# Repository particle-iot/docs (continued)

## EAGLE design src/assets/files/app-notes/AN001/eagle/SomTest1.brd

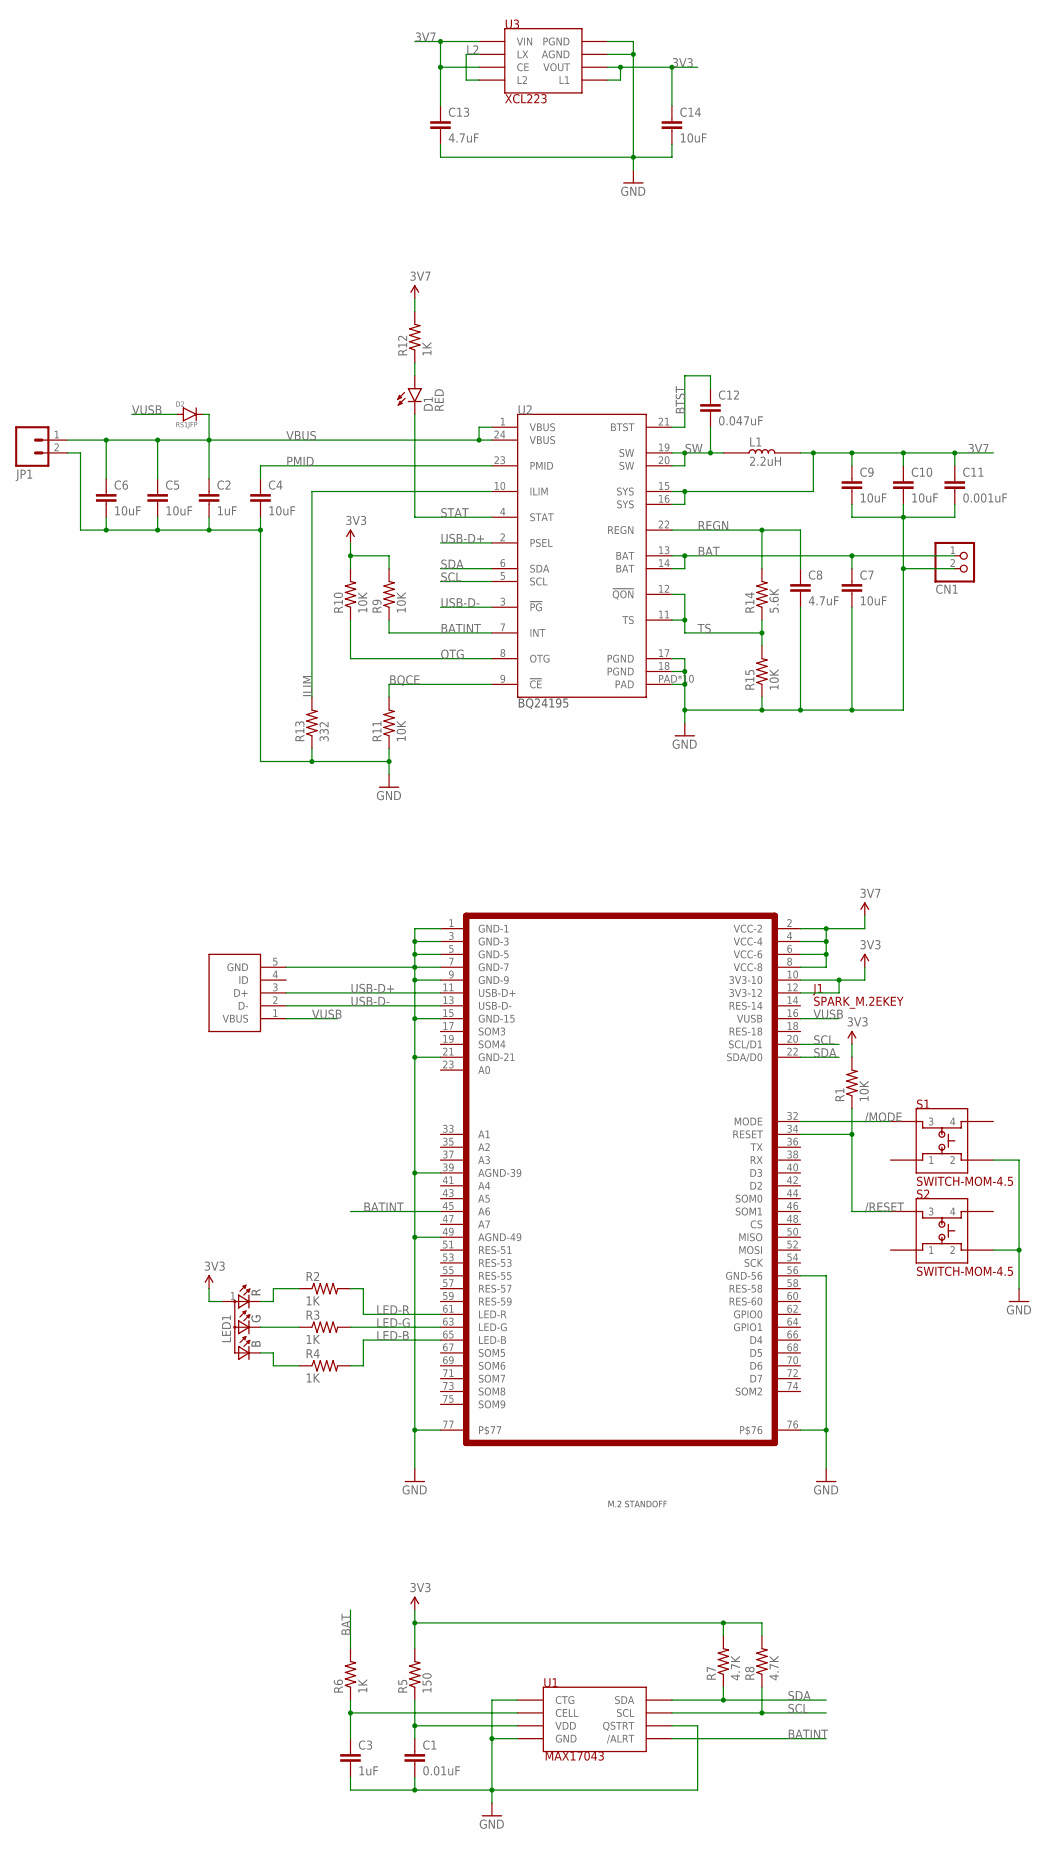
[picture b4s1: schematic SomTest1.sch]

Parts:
C1: 0.01uF; 0603-CAP
C2, C3: 1uF; 0603-CAP
C4, C5, C6, C7, C9, C10, C14: 10uF; 0603-CAP
C8, C13: 4.7uF; 0603-CAP
C11: 0.001uF; 0603-CAP
C12: 0.047uF; 0603-CAP
CN1: JST_2PIN-THM; JST-PH-2-THM
D1: RED; LED-0603
D2: RS1JFP; SOD-123HE-ON
J1: SPARK_M.2EKEY; SPARK_M.2EKEY-LESS-CREAM
JP1: M02PTH; 1X02
L1: 2.2uH; 1008-BOURNS
LED1: LED-RGB-CREE-SMD
R1, R9, R10, R11, R15: 10K; 0603-RES
R2, R3, R4, R6, R12: 1K; 0603-RES
R5: 150; 0603-RES
R7, R8: 4.7K; 0603-RES
R13: 332; 0603-RES
R14: 5.6K; 0603-RES
S1, S2: SWITCH-MOM-4.5
U1: MAX17043; 9UCSP-MAXIM
U2: BQ24195; 24VFQN-TI
U3: XCL223; REG-XCL223-LESS-CREAM
U$1: M2-STANDOFF
U$3: USB-MICRO-B-SOCKET-AMPHENOL; USB-B-SMT-AMPHENOL

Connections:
3V3: C14.1, J1.10 (3V3-10), J1.12 (3V3-12), LED1.1 (A), R1.2, R5.2, R7.2, R8.2, R9.2, R10.2, U3.3 (VOUT), U3.7 (L1)
3V7: C9.1, C10.1, C11.1, C13.1, J1.2 (VCC-2), J1.4 (VCC-4), J1.6 (VCC-6), J1.8 (VCC-8), L1.2, R12.2, U2.15 (SYS), U2.16 (SYS), U3.4 (CE), U3.6 (VIN)
/MODE: J1.32 (MODE), S1.3
/RESET: J1.34 (RESET), R1.1, S2.3
BAT: C7.1, CN1.1 (2), R6.2, U2.13 (BAT), U2.14 (BAT)
BATINT: J1.45 (A6), R9.1, U1.C1 (/ALRT), U2.7 (INT)
BQCE: R11.2, U2.9 (!CE)
BTST: C12.1, U2.21 (BTST)
GND: C1.2, C2.2, C3.2, C4.2, C5.2, C6.2, C7.2, C8.2, C9.2, C10.2, C11.2, C13.2, C14.2, CN1.2 (1), J1.1 (GND-1), J1.3 (GND-3), J1.5 (GND-5), J1.7 (GND-7), J1.9 (GND-9), J1.15 (GND-15), J1.21 (GND-21), J1.39 (AGND-39), J1.49 (AGND-49), J1.56 (GND-56), J1.76, J1.77, JP1.2, R11.1, R13.1, R15.1, S1.2, S2.2, U1.A3 (CTG), U1.B1 (QSTRT), U1.C3 (GND), U2.17 (PGND), U2.18 (PGND), U2.PAD, U2.PAD@1 (PAD), U2.PAD@2 (PAD), U2.PAD@3 (PAD), U2.PAD@4 (PAD), U2.PAD@5 (PAD), U2.PAD@6 (PAD), U2.PAD@7 (PAD), U2.PAD@8 (PAD), U2.PAD@9 (PAD), U3.1 (PGND), U3.2 (AGND), U$3.5 (GND)
ILIM: R13.2, U2.10 (ILIM)
L2: U3.5 (LX), U3.8 (L2)
LED-B: J1.65 (LED-B), R4.2
LED-G: J1.63 (LED-G), R3.2
LED-R: J1.61 (LED-R), R2.2
unnamed: LED1.3 (G), R3.1
unnamed: C3.1, R6.1, U1.B3 (CELL)
unnamed: C1.1, R5.1, U1.C2 (VDD)
unnamed: LED1.4 (R), R2.1
unnamed: D1.A, R12.1
unnamed: LED1.2 (B), R4.1
OTG: R10.1, U2.8 (OTG)
PMID: C4.1, U2.23 (PMID)
REGN: C8.1, R14.2, U2.22 (REGN)
SCL: J1.20 (SCL/D1), R8.1, U1.A2 (SCL), U2.5 (SCL)
SDA: J1.22 (SDA/D0), R7.1, U1.A1 (SDA), U2.6 (SDA)
STAT: D1.C, U2.4 (STAT)
SW: C12.2, L1.1, U2.19 (SW), U2.20 (SW)
TS: R14.1, R15.2, U2.11 (TS), U2.12 (!QON)
USB-D+: J1.11 (USB-D+), U2.2 (PSEL), U$3.3 (D+)
USB-D-: J1.13 (USB-D-), U2.3 (!PG), U$3.2 (D-)
VBUS: C2.1, C5.1, C6.1, D2.1 (CATHODE), JP1.1, U2.1 (VBUS), U2.24 (VBUS)
VUSB: D2.2 (ANODE), J1.16 (VUSB), U$3.1 (VBUS)

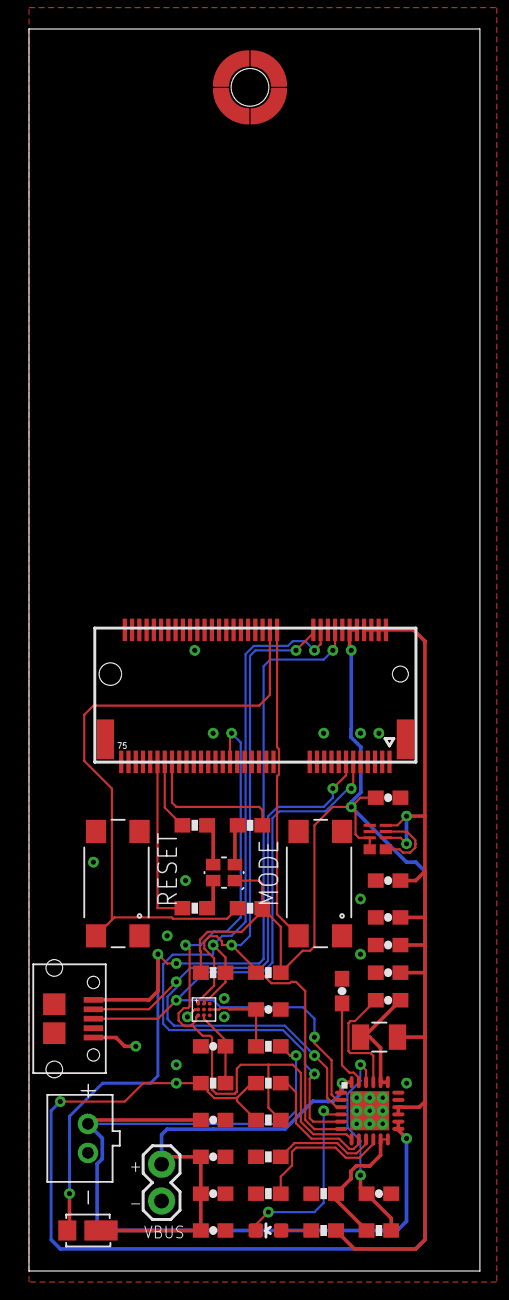
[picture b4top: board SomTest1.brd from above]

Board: 2 copper layers, 31.1 x 85.6 mm, 43 parts (0 on the bottom side), 32 nets.

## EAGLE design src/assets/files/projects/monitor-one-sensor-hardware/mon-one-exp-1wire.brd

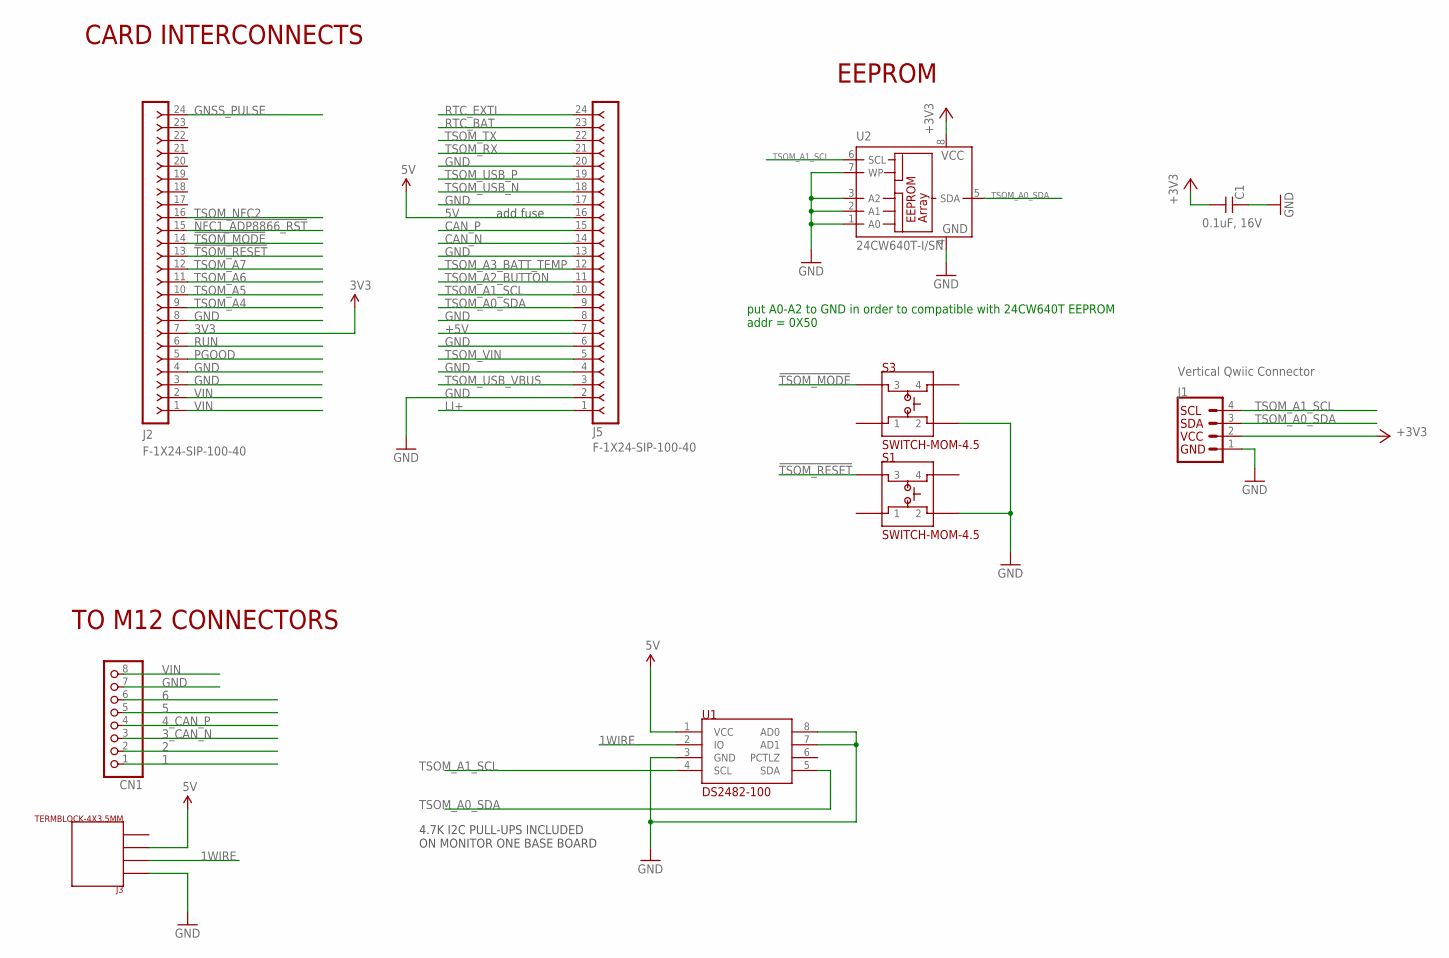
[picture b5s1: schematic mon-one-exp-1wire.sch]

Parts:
C1: 0.1uF, 16V; C0603_P
CN1: JST_8PIN; JSTPH8
J1: Vertical Qwiic Connector; JST04_1MM_VERT
J2, J5: F-1X24-SIP-100-40; SIP-100-24-40
J3: TERMBLOCK-4X3.5MM
S1, S3: SWITCH-MOM-4.5
U1: DS2482-100; 8-SOIC-MAXIM
U2: 24CW640T-I/SN; SO-08

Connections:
1: CN1.1
1WIRE: J3.2, U1.2 (IO)
2: CN1.2
3V3: C1.1, J1.2, J2.7, U2.8 (VCC)
3_CAN_N: CN1.3
4_CAN_P: CN1.4
5: CN1.5
5V: J3.3, J5.16, U1.1 (VCC)
6: CN1.6
!NFC1_ADP8866_RST: J2.15
!TSOM_MODE: J2.14, S3.3
!TSOM_RESET: J2.13, S1.3
+5V: J5.7
CAN_N: J5.14
CAN_P: J5.15
GND: C1.2, CN1.7, J1.1, J2.3, J2.4, J2.8, J3.1, J5.2, J5.4, J5.6, J5.8, J5.13, J5.17, J5.20, S1.2, S3.2, U1.3 (GND), U1.7 (AD1), U1.8 (AD0), U2.1 (A0), U2.2 (A1), U2.3 (A2), U2.4 (GND), U2.7 (WP)
GNSS_PULSE: J2.24
LI+: J5.1
PGOOD: J2.5
RTC_BAT: J5.23
RTC_EXTI: J5.24
RUN: J2.6
TSOM_A0_SDA: J1.3, J5.9, U1.5 (SDA), U2.5 (SDA)
TSOM_A1_SCL: J1.4, J5.10, U1.4 (SCL), U2.6 (SCL)
TSOM_A2_BUTTON: J5.11
TSOM_A3_BATT_TEMP: J5.12
TSOM_A4: J2.9
TSOM_A5: J2.10
TSOM_A6: J2.11
TSOM_A7: J2.12
TSOM_NFC2: J2.16
TSOM_RX: J5.21
TSOM_TX: J5.22
TSOM_USB_N: J5.18
TSOM_USB_P: J5.19
TSOM_USB_VBUS: J5.3
TSOM_VIN: J5.5
VIN: CN1.8, J2.1, J2.2

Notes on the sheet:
add fuse
CARD INTERCONNECTS
EEPROM
put A0-A2 to GND in order to compatible with 24CW640T EEPROM addr = 0X50
TO M12 CONNECTORS
4.7K I2C PULL-UPS INCLUDED ON MONITOR ONE BASE BOARD

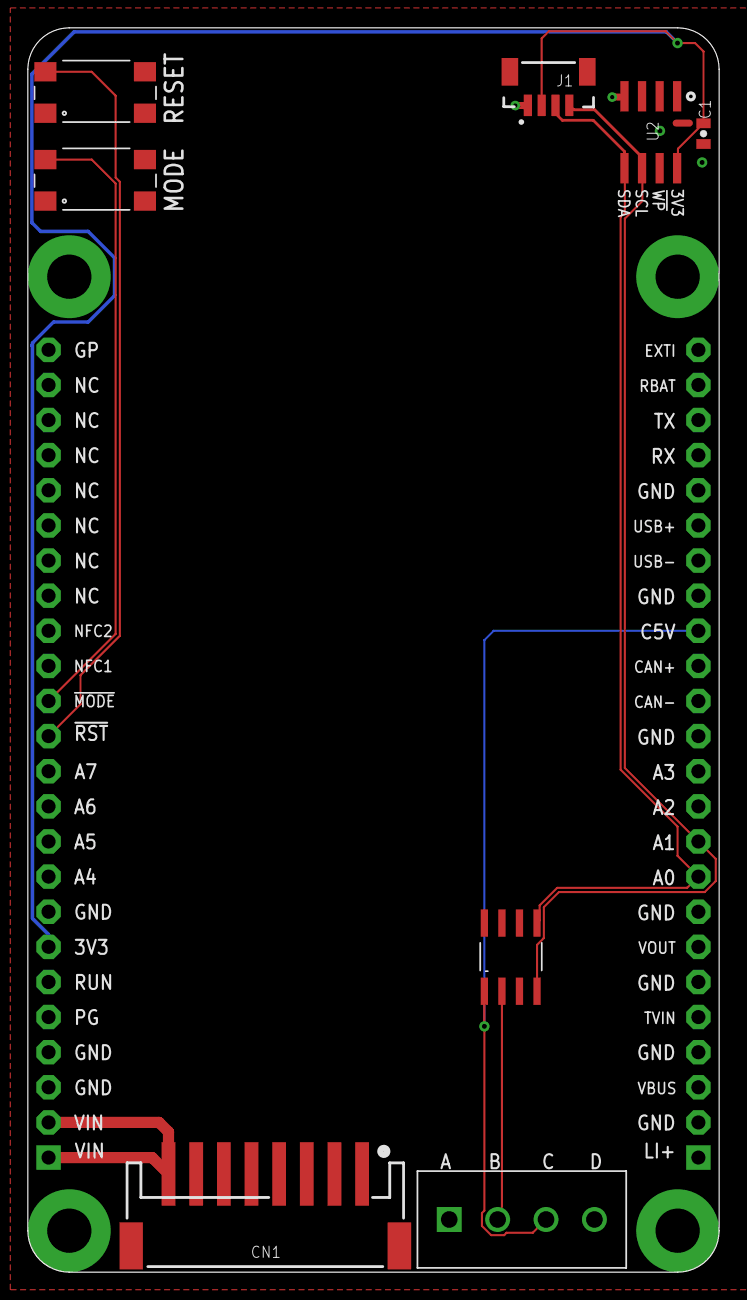
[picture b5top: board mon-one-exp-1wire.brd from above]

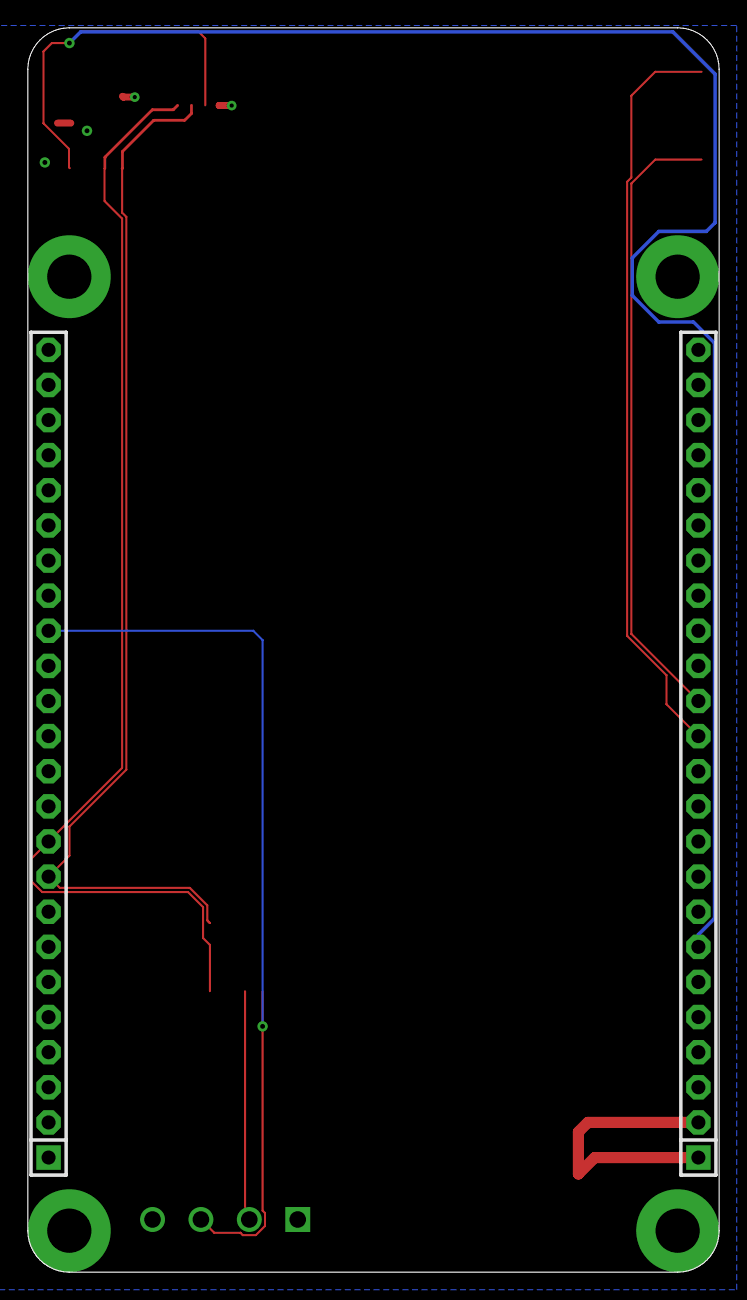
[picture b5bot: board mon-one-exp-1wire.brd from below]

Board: 2 copper layers, 50.0 x 90.0 mm, 10 parts (2 on the bottom side), 9 nets.

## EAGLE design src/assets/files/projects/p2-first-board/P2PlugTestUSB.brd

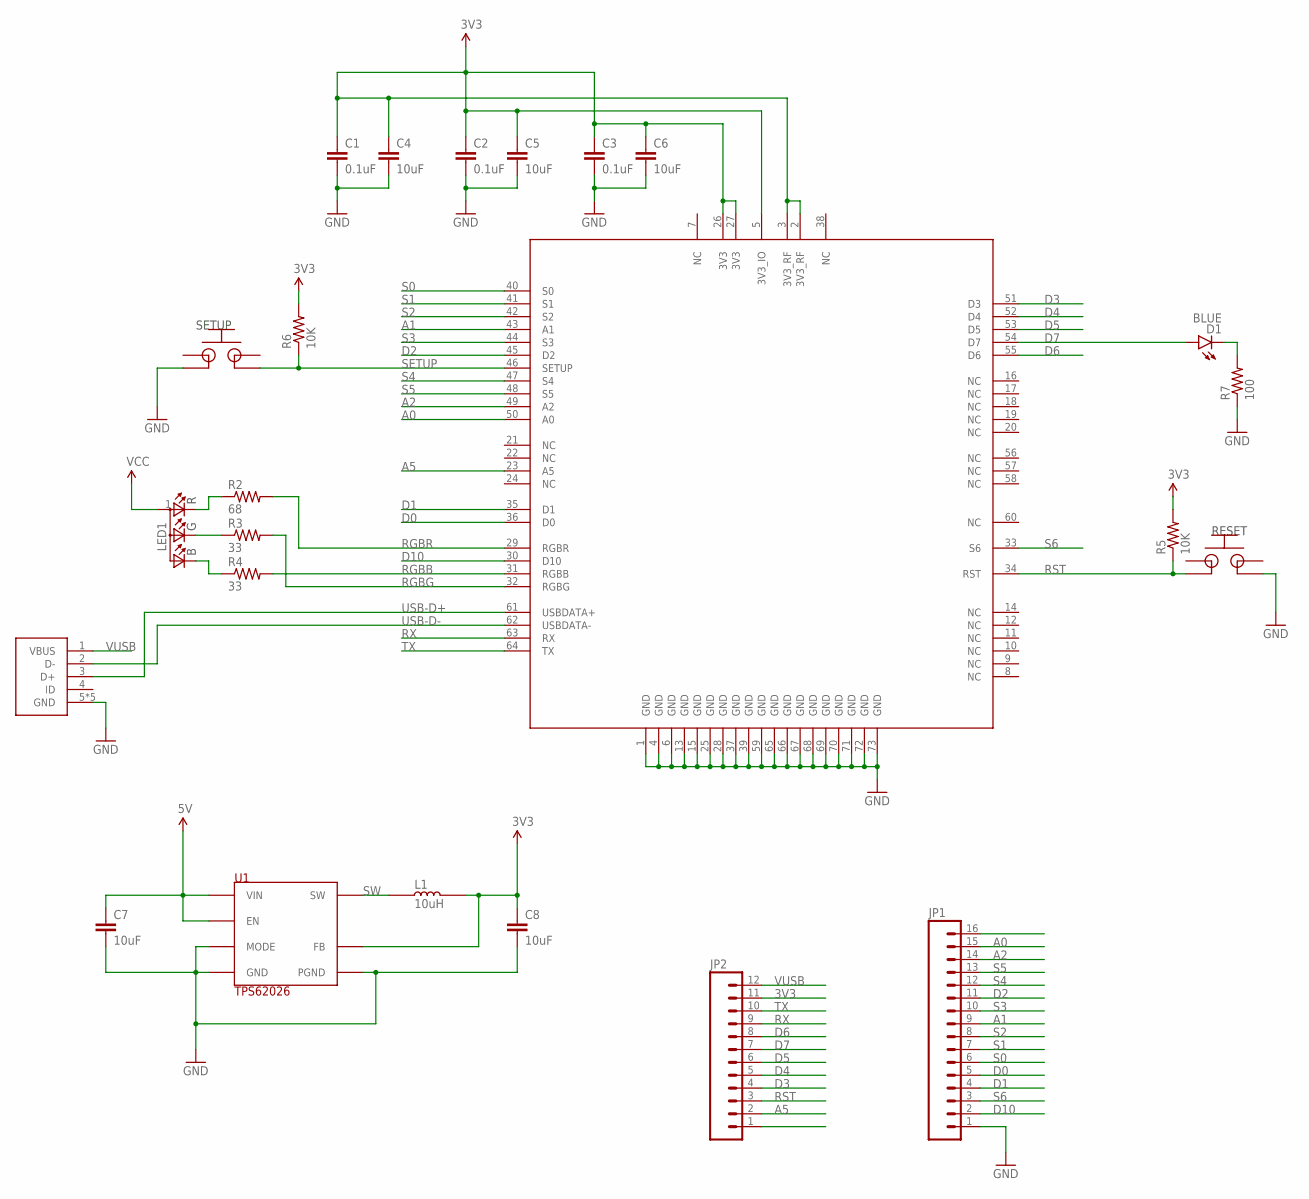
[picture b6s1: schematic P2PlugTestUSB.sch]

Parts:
C1, C2, C3: 0.1uF; 0603-CAP
C4, C5, C6, C7, C8: 10uF; 0603-CAP
D1: BLUE; LED-0603
JP1: M16PTH; 1X16
JP2: M12PTH; 1X12
L1: 10uH; BOURNS-INDUCTOR-3X3
LED1: LED-RGB-CREE-SMD
R2: 68; 0603-RES
R3, R4: 33; 0603-RES
R5, R6: 10K; 0603-RES
R7: 100; 0603-RES
U1: TPS62026; 10-HVSSOP-TI
U$1: USB-MICRO-B-SOCKET-AMPHENOL; USB-B-SMT-AMPHENOL
U$3: P2
U$4, U$5: SWITCH-PTS645

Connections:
3V3: C1.1, C2.1, C3.1, C4.1, C5.1, C6.1, C8.1, JP2.11, L1.2, LED1.1 (A), R5.2, R6.2, U1.5 (FB), U$3.2 (3V3_RF), U$3.3 (3V3_RF), U$3.5 (3V3_IO), U$3.26 (3V3), U$3.27 (3V3)
A0: JP1.15, U$3.50 (A0)
A1: JP1.9, U$3.43 (A1)
A2: JP1.14, U$3.49 (A2)
A5: JP2.2, U$3.23 (A5)
D0: JP1.5, U$3.36 (D0)
D1: JP1.4, U$3.35 (D1)
D2: JP1.11, U$3.45 (D2)
D3: JP2.4, U$3.51 (D3)
D4: JP2.5, U$3.52 (D4)
D5: JP2.6, U$3.53 (D5)
D6: JP2.8, U$3.55 (D6)
D7: D1.A, JP2.7, U$3.54 (D7)
D10: JP1.2, U$3.30 (D10)
GND: C1.2, C2.2, C3.2, C4.2, C5.2, C6.2, C7.2, C8.2, JP1.1, R7.1, U1.4 (GND), U1.6 (MODE), U1.9 (PGND), U1.10 (PGND), U1.P (GND), U$1.5 (GND), U$1.P$1 (GND), U$1.P$2 (GND), U$1.P$6 (GND), U$1.P$7 (GND), U$3.1 (GND), U$3.4 (GND), U$3.6 (GND), U$3.13 (GND), U$3.15 (GND), U$3.25 (GND), U$3.28 (GND), U$3.37 (GND), U$3.39 (GND), U$3.59 (GND), U$3.65 (GND), U$3.66 (GND), U$3.67 (GND), U$3.68 (GND), U$3.69 (GND), U$3.70 (GND), U$3.71 (GND), U$3.72 (GND), U$3.73 (GND), U$4.2, U$5.4
unnamed: D1.C, R7.2
unnamed: LED1.4 (R), R2.1
unnamed: LED1.3 (G), R3.1
unnamed: LED1.2 (B), R4.1
RGBB: R4.2, U$3.31 (RGBB)
RGBG: R3.2, U$3.32 (RGBG)
RGBR: R2.2, U$3.29 (RGBR)
RST: JP2.3, R5.1, U$3.34 (RST), U$5.2
RX: JP2.9, U$3.63 (RX)
S0: JP1.6, U$3.40 (S0)
S1: JP1.7, U$3.41 (S1)
S2: JP1.8, U$3.42 (S2)
S3: JP1.10, U$3.44 (S3)
S4: JP1.12, U$3.47 (S4)
S5: JP1.13, U$3.48 (S5)
S6: JP1.3, U$3.33 (S6)
SETUP: R6.1, U$3.46 (SETUP), U$4.4
SW: L1.1, U1.7 (SW), U1.8 (SW)
TX: JP2.10, U$3.64 (TX)
USB-D+: U$1.3 (D+), U$3.61 (USBDATA+)
USB-D-: U$1.2 (D-), U$3.62 (USBDATA-)
VUSB: C7.1, JP2.12, U1.1 (EN), U1.2 (VIN), U1.3 (VIN), U$1.1 (VBUS)

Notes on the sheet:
SETUP
RESET

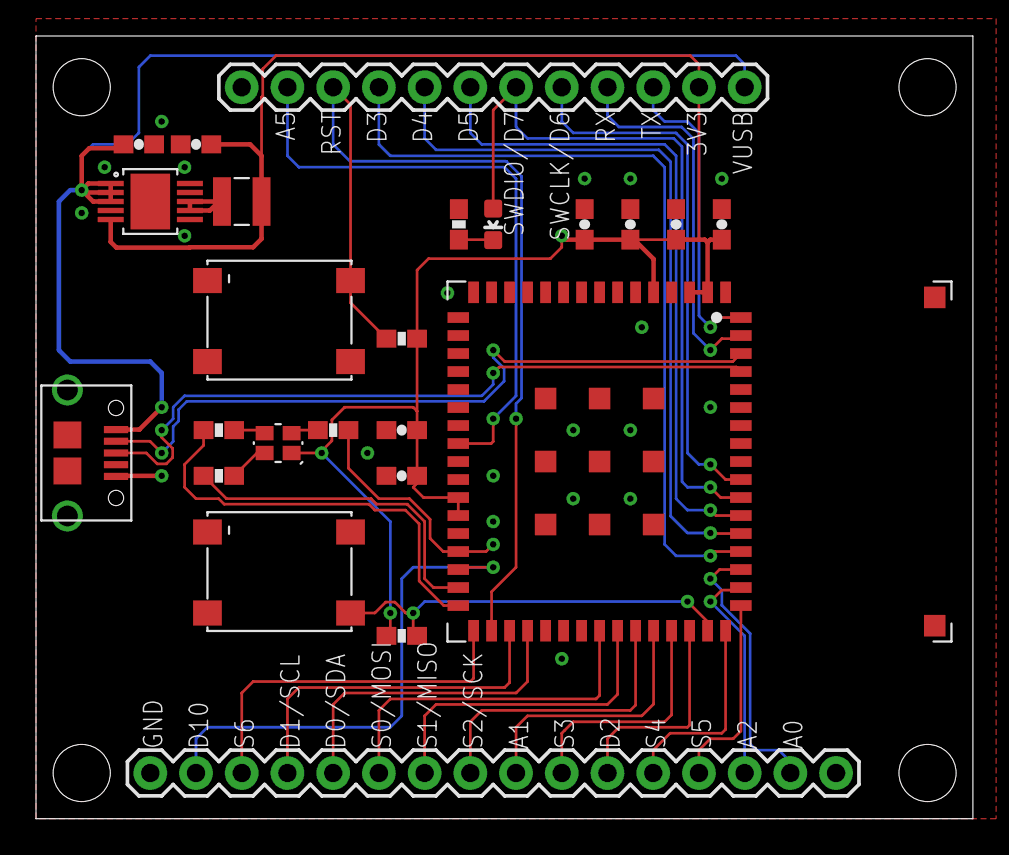
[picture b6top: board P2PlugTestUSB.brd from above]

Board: 2 copper layers, 52.0 x 43.5 mm, 24 parts (0 on the bottom side), 37 nets.

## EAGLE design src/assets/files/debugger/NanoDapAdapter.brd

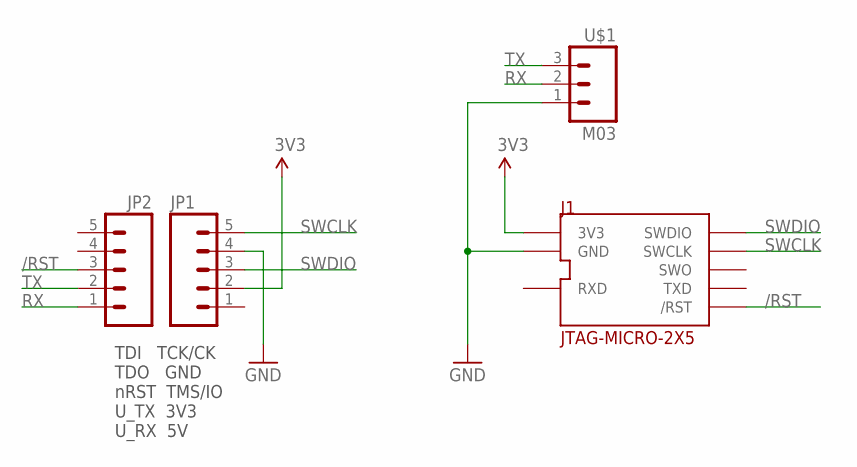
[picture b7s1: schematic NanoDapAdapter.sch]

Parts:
J1: JTAG-MICRO-2X5
JP1, JP2: M05PTH; 1X05
U$1: M03; 1X03

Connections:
3V3: J1.1 (3V3), JP1.2
/RST: J1.10 (/RST), JP2.3
GND: J1.3 (GND), J1.5 (GND), J1.9 (GND), JP1.4, U$1.1
RX: JP2.1, U$1.2
SWCLK: J1.4 (SWCLK), JP1.5
SWDIO: J1.2 (SWDIO), JP1.3
TX: JP2.2, U$1.3

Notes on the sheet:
TDI TCK/CK TDO GND nRST TMS/IO U_TX 3V3 U_RX 5V

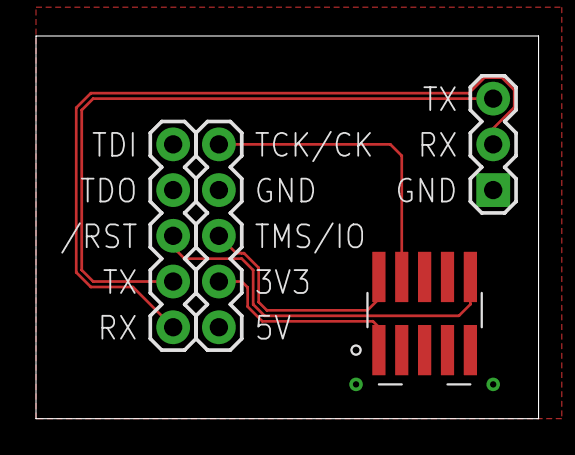
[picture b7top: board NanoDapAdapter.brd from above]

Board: 2 copper layers, 27.9 x 21.3 mm, 4 parts (0 on the bottom side), 7 nets.

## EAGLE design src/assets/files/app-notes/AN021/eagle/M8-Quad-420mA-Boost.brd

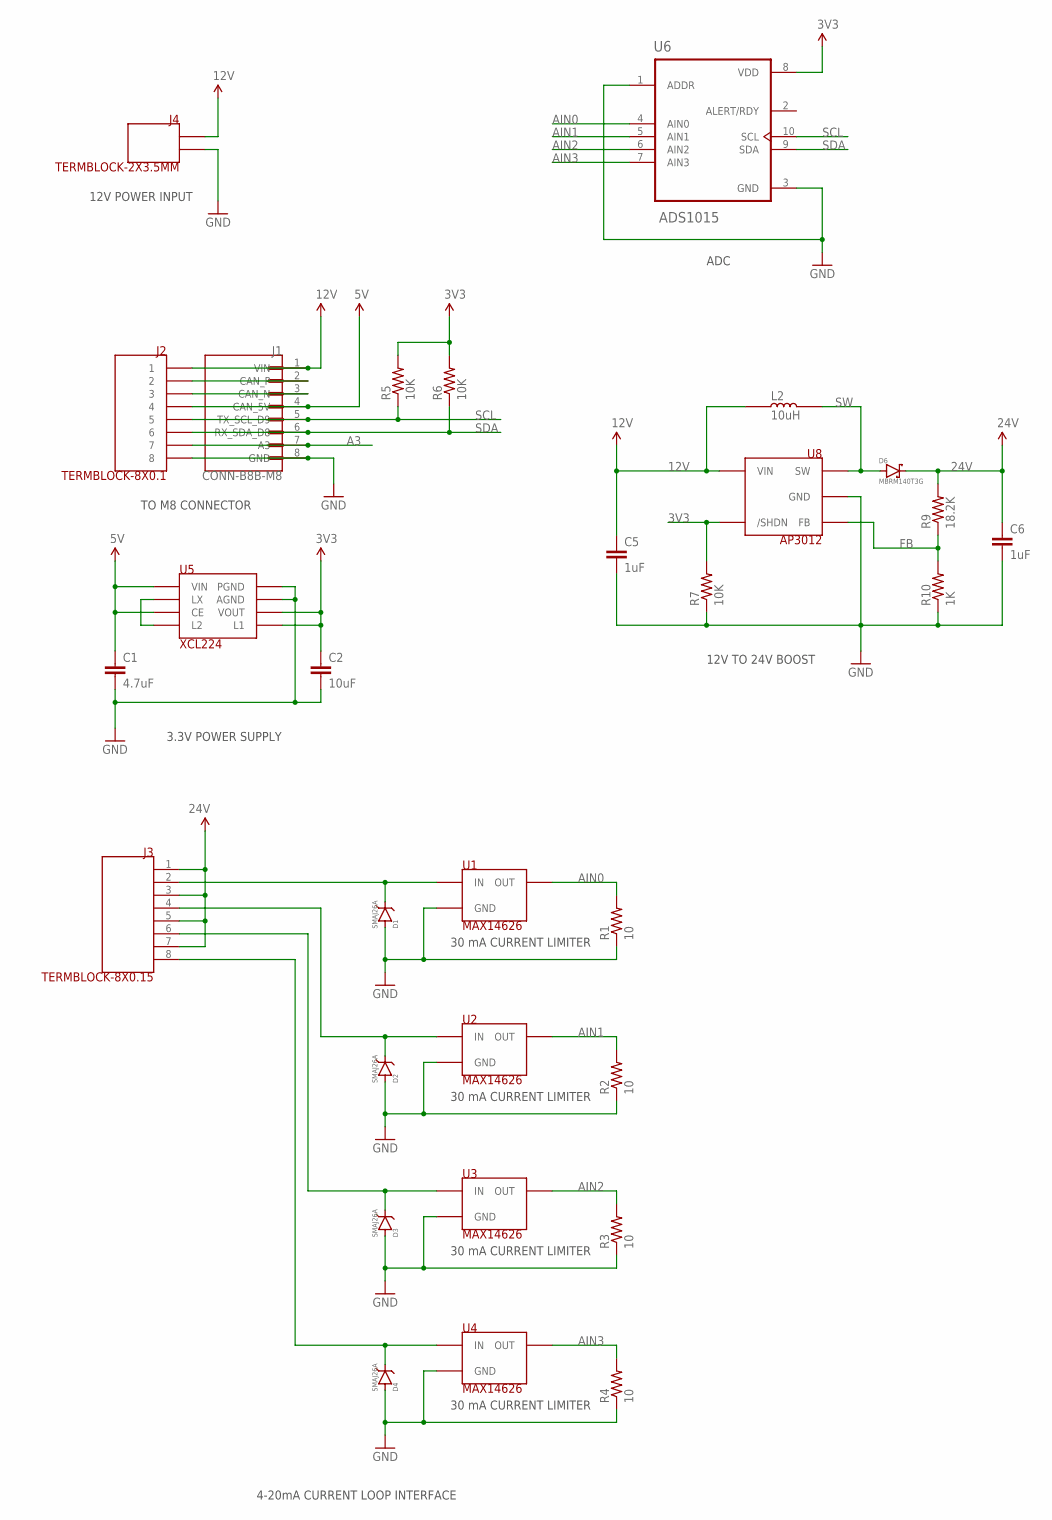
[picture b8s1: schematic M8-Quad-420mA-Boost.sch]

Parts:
C1: 4.7uF; 0603-CAP
C2: 10uF; 0603-CAP
C5, C6: 1uF; 0603-CAP
D1, D2, D3, D4: SMAJ26A; DO-214AC-LITTELFUSE
D6: MBRM140T3G
J1: CONN-B8B-M8; JST_B8B-PH-SM4-TB(LF)(SN)
J2: TERMBLOCK-8X0.1
J3: TERMBLOCK-8X0.15
J4: TERMBLOCK-2X3.5MM
L2: 10uH; BOURNS-INDUCTOR-3X3
R1, R2, R3, R4: 10; 0603-RES
R5, R6, R7: 10K; 0603-RES
R9: 18.2K; 0603-RES
R10: 1K; 0603-RES
U1, U2, U3, U4: MAX14626; 6-TDFN-MAXIM
U5: XCL224; REG-XCL223-LESS-CREAM
U6: ADS1015; SOP50P490X110-10N
U8: AP3012; SOT-23-5

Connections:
3V3: C2.1, R5.2, R6.2, R7.2, U5.3 (VOUT), U5.7 (L1), U6.8 (VDD), U8.4 (/SHDN)
5V: C1.1, J1.4 (CAN_5V), J2.P$4 (4), U5.4 (CE), U5.6 (VIN)
12V: C5.1, J1.1 (VIN), J2.P$1 (1), J4.1, L2.1, U8.5 (VIN)
24V: C6.1, D6.1 (CATHODE), J3.1, J3.3, J3.5, J3.7, R9.2
A3: J1.7 (A3), J2.P$7 (7)
AIN0: R1.2, U1.6 (OUT), U6.4 (AIN0)
AIN1: R2.2, U2.6 (OUT), U6.5 (AIN1)
AIN2: R3.2, U3.6 (OUT), U6.6 (AIN2)
AIN3: R4.2, U4.6 (OUT), U6.7 (AIN3)
CAN_N: J1.3 (CAN_N), J2.P$3 (3)
CAN_P: J1.2 (CAN_P), J2.P$2 (2)
FB: R9.1, R10.2, U8.3 (FB)
GND: C1.2, C2.2, C5.2, C6.2, D1.A (ANODE), D2.A (ANODE), D3.A (ANODE), D4.A (ANODE), J1.8 (GND), J2.P$8 (8), J4.2, R1.1, R2.1, R3.1, R4.1, R7.1, R10.1, U1.2 (GND), U1.3 (GND), U1.4 (GND), U1.5 (GND), U1.EP (GND), U2.2 (GND), U2.3 (GND), U2.4 (GND), U2.5 (GND), U2.EP (GND), U3.2 (GND), U3.3 (GND), U3.4 (GND), U3.5 (GND), U3.EP (GND), U4.2 (GND), U4.3 (GND), U4.4 (GND), U4.5 (GND), U4.EP (GND), U5.1 (PGND), U5.2 (AGND), U6.1 (ADDR), U6.3 (GND), U8.2 (GND)
LX: U5.5 (LX), U5.8 (L2)
SCL: J1.5 (TX_SCL_D9), J2.P$5 (5), R5.1, U6.10 (SCL)
SDA: J1.6 (RX_SDA_D8), J2.P$6 (6), R6.1, U6.9 (SDA)
SEN1: D1.C (CATHODE), J3.2, U1.1 (IN)
SEN2: D2.C (CATHODE), J3.4, U2.1 (IN)
SEN3: D3.C (CATHODE), J3.6, U3.1 (IN)
SEN4: D4.C (CATHODE), J3.8, U4.1 (IN)
SW: D6.2 (ANODE), L2.2, U8.1 (SW)

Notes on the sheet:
TO M8 CONNECTOR
3.3V POWER SUPPLY
ADC
30 mA CURRENT LIMITER
4-20mA CURRENT LOOP INTERFACE
12V TO 24V BOOST
12V POWER INPUT

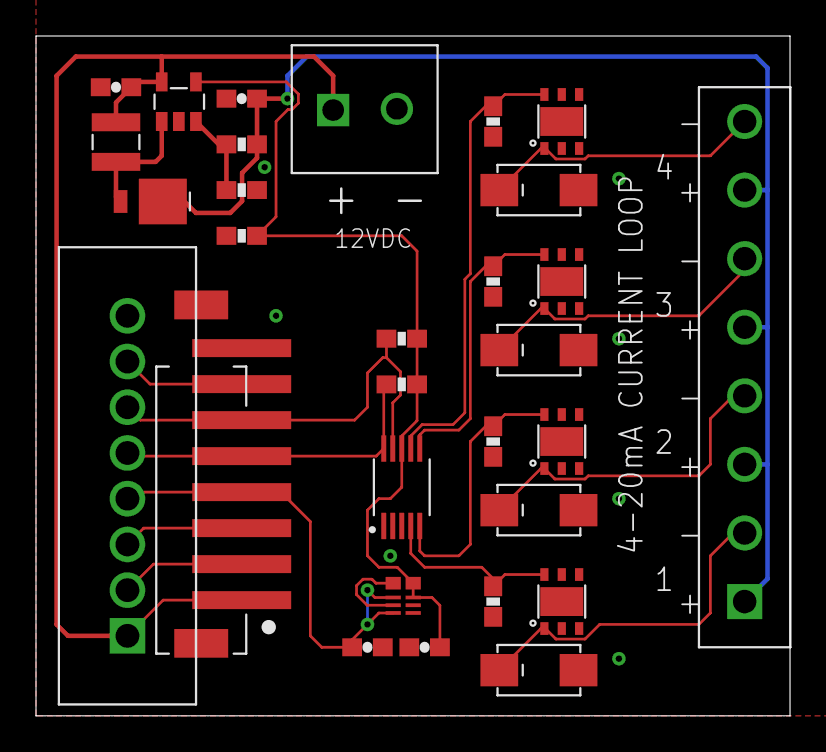
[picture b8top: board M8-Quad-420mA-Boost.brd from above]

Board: 2 copper layers, 41.9 x 37.8 mm, 30 parts (0 on the bottom side), 21 nets.
